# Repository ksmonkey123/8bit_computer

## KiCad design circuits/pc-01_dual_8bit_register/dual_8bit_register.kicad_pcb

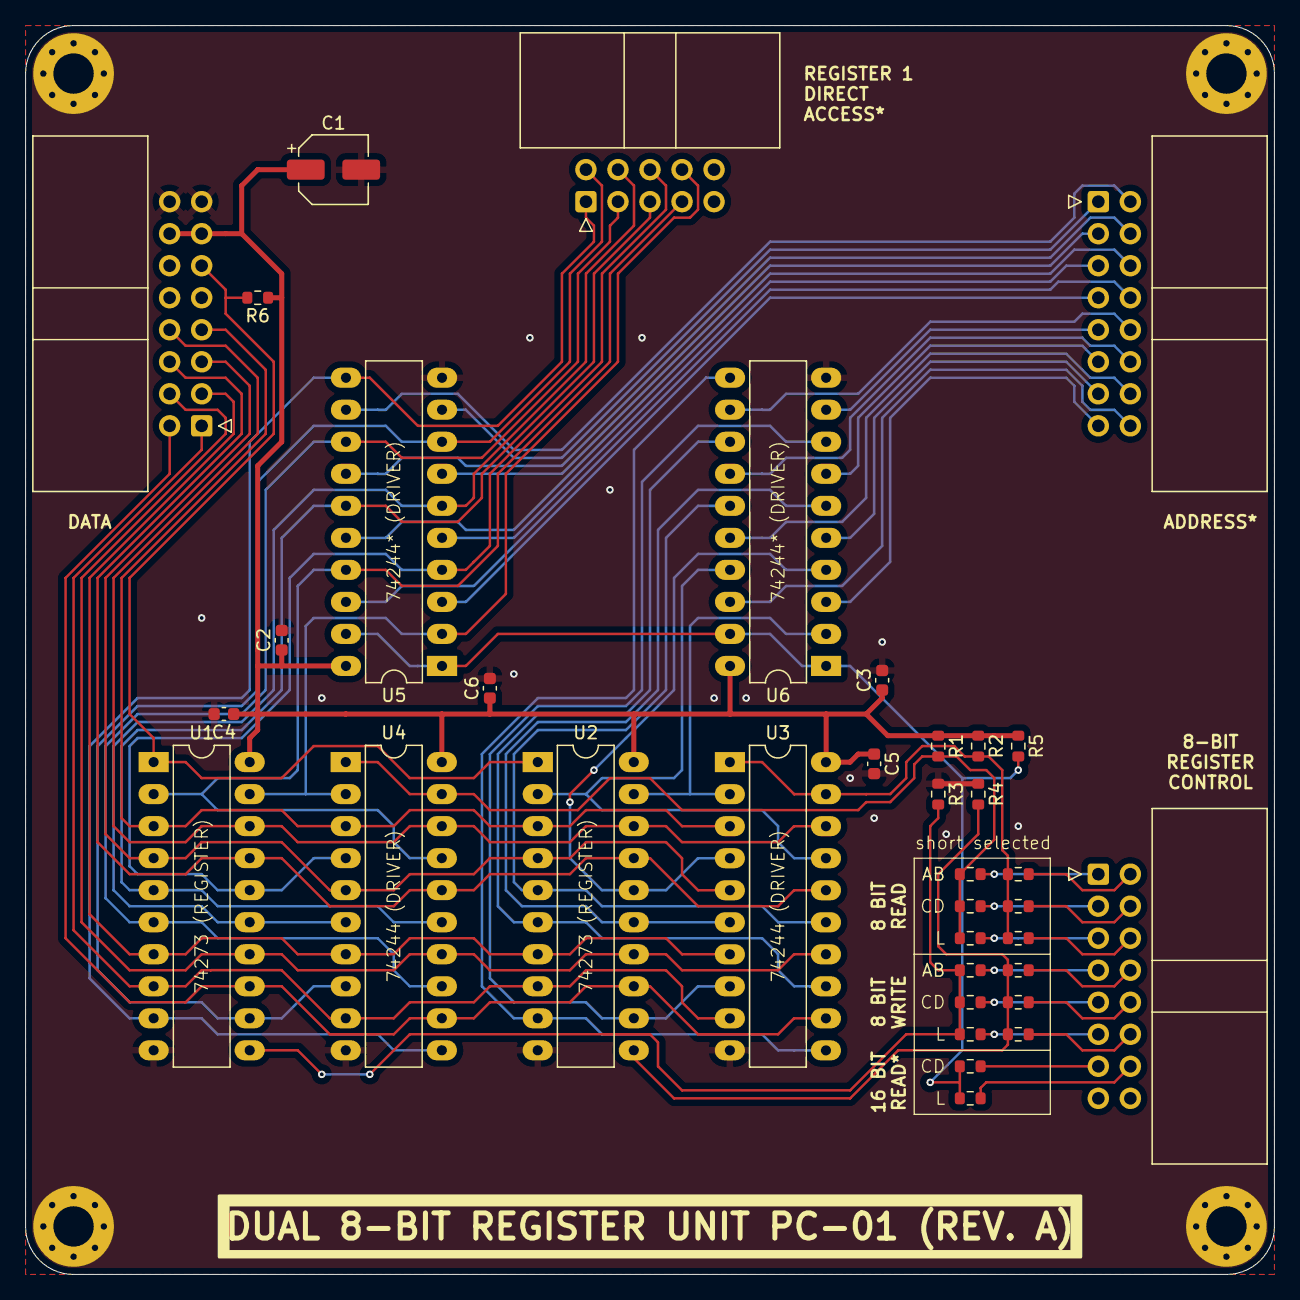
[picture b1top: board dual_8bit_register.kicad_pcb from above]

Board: 2 copper layers, 99.1 x 99.1 mm, 40 parts (0 on the bottom side), 62 nets.

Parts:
ADDRESS_BUS1: Conn_01x16; IDC-Header_2x08_P2.54mm_Horizontal
C1: C_Polarized; CP_Elec_5x5.3
C2, C3, C4, C5, C6: C; C_0603_1608Metric
CTRL_BUS1: Conn_01x16; IDC-Header_2x08_P2.54mm_Horizontal
DATA_BUS1: Conn_01x16; IDC-Header_2x08_P2.54mm_Horizontal
H1, H2, H3, H4: MountingHole_Pad; MountingHole_3.2mm_M3_Pad_Via
J1: Conn_01x10; IDC-Header_2x05_P2.54mm_Horizontal
R1, R2, R3, R4, R5, R6: R; R_0603_1608Metric
R_adrCD1: R; R_0603_1608Metric
R_adrL1: R; R_0603_1608Metric
R_readA1: R; R_0603_1608Metric
R_readB1: R; R_0603_1608Metric
R_readC1: R; R_0603_1608Metric
R_readD1: R; R_0603_1608Metric
R_readL1, R_readL2: R; R_0603_1608Metric
R_writeA1: R; R_0603_1608Metric
R_writeB1: R; R_0603_1608Metric
R_writeC1: R; R_0603_1608Metric
R_writeD1: R; R_0603_1608Metric
R_writeL1, R_writeL2: R; R_0603_1608Metric
U1, U2: 74HC273; DIP-20_W7.62mm_LongPads
U3, U4, U5, U6: 74HC244; DIP-20_W7.62mm_LongPads

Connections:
/adr0: ADDRESS_BUS1.1, U5.9 (2Y3)
/adr1: ADDRESS_BUS1.2, U5.12 (1Y3)
/adr2: ADDRESS_BUS1.3, U5.7 (2Y2)
/adr3: ADDRESS_BUS1.4, U5.14 (1Y2)
/adr4: ADDRESS_BUS1.5, U5.5 (2Y1)
/adr5: ADDRESS_BUS1.6, U5.16 (1Y1)
/adr6: ADDRESS_BUS1.7, U5.3 (2Y0)
/adr7: ADDRESS_BUS1.8, U5.18 (1Y0)
/adr8: ADDRESS_BUS1.9, U6.9 (2Y3)
/adr9: ADDRESS_BUS1.10, U6.12 (1Y3)
/adr10: ADDRESS_BUS1.11, U6.7 (2Y2)
/adr11: ADDRESS_BUS1.12, U6.14 (1Y2)
/adr12: ADDRESS_BUS1.13, U6.5 (2Y1)
/adr13: ADDRESS_BUS1.14, U6.16 (1Y1)
/adr14: ADDRESS_BUS1.15, U6.3 (2Y0)
/adr15: ADDRESS_BUS1.16, U6.18 (1Y0)
/d0: DATA_BUS1.1, U1.8 (D3), U2.8 (D3), U3.9 (2Y3), U4.9 (2Y3)
/d1: DATA_BUS1.2, U1.13 (D4), U2.13 (D4), U3.12 (1Y3), U4.12 (1Y3)
/d2: DATA_BUS1.3, U1.7 (D2), U2.7 (D2), U3.7 (2Y2), U4.7 (2Y2)
/d3: DATA_BUS1.4, U1.14 (D5), U2.14 (D5), U3.14 (1Y2), U4.14 (1Y2)
/d4: DATA_BUS1.5, U1.4 (D1), U2.4 (D1), U3.5 (2Y1), U4.5 (2Y1)
/d5: DATA_BUS1.6, U1.17 (D6), U2.17 (D6), U3.16 (1Y1), U4.16 (1Y1)
/d6: DATA_BUS1.7, U1.3 (D0), U2.3 (D0), U3.3 (2Y0), U4.3 (2Y0)
/d7: DATA_BUS1.8, U1.18 (D7), U2.18 (D7), U3.18 (1Y0), U4.18 (1Y0)
/writeA: CTRL_BUS1.7, R_writeA1.1
/writeB: CTRL_BUS1.8, R_writeB1.1
/writeC: CTRL_BUS1.9, R_writeC1.1
/writeD: CTRL_BUS1.10, R_writeD1.1
/writeL1: CTRL_BUS1.11, R_writeL1.1
/writeL2: CTRL_BUS1.12, R_writeL2.1
/~adrCD: CTRL_BUS1.13, R_adrCD1.2
/~adrL: CTRL_BUS1.14, R_adrL1.2
/~readA: CTRL_BUS1.1, R_readA1.2
/~readB: CTRL_BUS1.2, R_readB1.2
/~readC: CTRL_BUS1.3, R_readC1.2
/~readD: CTRL_BUS1.4, R_readD1.2
/~readL1: CTRL_BUS1.5, R_readL1.2
/~readL2: CTRL_BUS1.6, R_readL2.2
/~reset: DATA_BUS1.11, R6.2, U1.1 (~Mr), U2.1 (~Mr)
GND: C1.2, C2.2, C3.2, C4.2, C5.2, C6.2, DATA_BUS1.15, DATA_BUS1.16, H1.1, H2.1, H3.1, H4.1, R3.1, R4.1, U1.10 (GND), U2.10 (GND), U3.10 (GND), U4.10 (GND), U5.10 (GND), U6.10 (GND)
unnamed: J1.1, U1.9 (Q3), U4.11 (2A3), U5.11 (2A3)
unnamed: J1.2, U1.12 (Q4), U4.8 (1A3), U5.8 (1A3)
unnamed: J1.3, U1.6 (Q2), U4.13 (2A2), U5.13 (2A2)
unnamed: J1.4, U1.15 (Q5), U4.6 (1A2), U5.6 (1A2)
unnamed: J1.5, U1.5 (Q1), U4.15 (2A1), U5.15 (2A1)
unnamed: J1.6, U1.16 (Q6), U4.4 (1A1), U5.4 (1A1)
unnamed: J1.7, U1.2 (Q0), U4.17 (2A0), U5.17 (2A0)
unnamed: J1.8, U1.19 (Q7), U4.2 (1A0), U5.2 (1A0)
unnamed: R3.2, R_writeA1.2, R_writeC1.2, R_writeL1.2, U1.11 (Cp)
unnamed: R4.2, R_writeB1.2, R_writeD1.2, R_writeL2.2, U2.11 (Cp)
unnamed: U2.2 (Q0), U3.17 (2A0), U6.17 (2A0)
unnamed: U2.5 (Q1), U3.15 (2A1), U6.15 (2A1)
unnamed: U2.6 (Q2), U3.13 (2A2), U6.13 (2A2)
unnamed: U2.9 (Q3), U3.11 (2A3), U6.11 (2A3)
unnamed: U2.12 (Q4), U3.8 (1A3), U6.8 (1A3)
unnamed: U2.15 (Q5), U3.6 (1A2), U6.6 (1A2)
unnamed: U2.16 (Q6), U3.4 (1A1), U6.4 (1A1)
unnamed: U2.19 (Q7), U3.2 (1A0), U6.2 (1A0)
unnamed: R2.2, R_readB1.1, R_readD1.1, R_readL2.1, U3.1 (1OE), U3.19 (2OE)
unnamed: R1.2, R_readA1.1, R_readC1.1, R_readL1.1, U4.1 (1OE), U4.19 (2OE)
unnamed: R5.2, R_adrCD1.1, R_adrL1.1, U5.1 (1OE), U5.19 (2OE), U6.1 (1OE), U6.19 (2OE)
VCC: C1.1, C2.1, C3.1, C4.1, C5.1, C6.1, DATA_BUS1.13, DATA_BUS1.14, R1.1, R2.1, R5.1, R6.1, U1.20 (VCC), U2.20 (VCC), U3.20 (VCC), U4.20 (VCC), U5.20 (VCC), U6.20 (VCC)

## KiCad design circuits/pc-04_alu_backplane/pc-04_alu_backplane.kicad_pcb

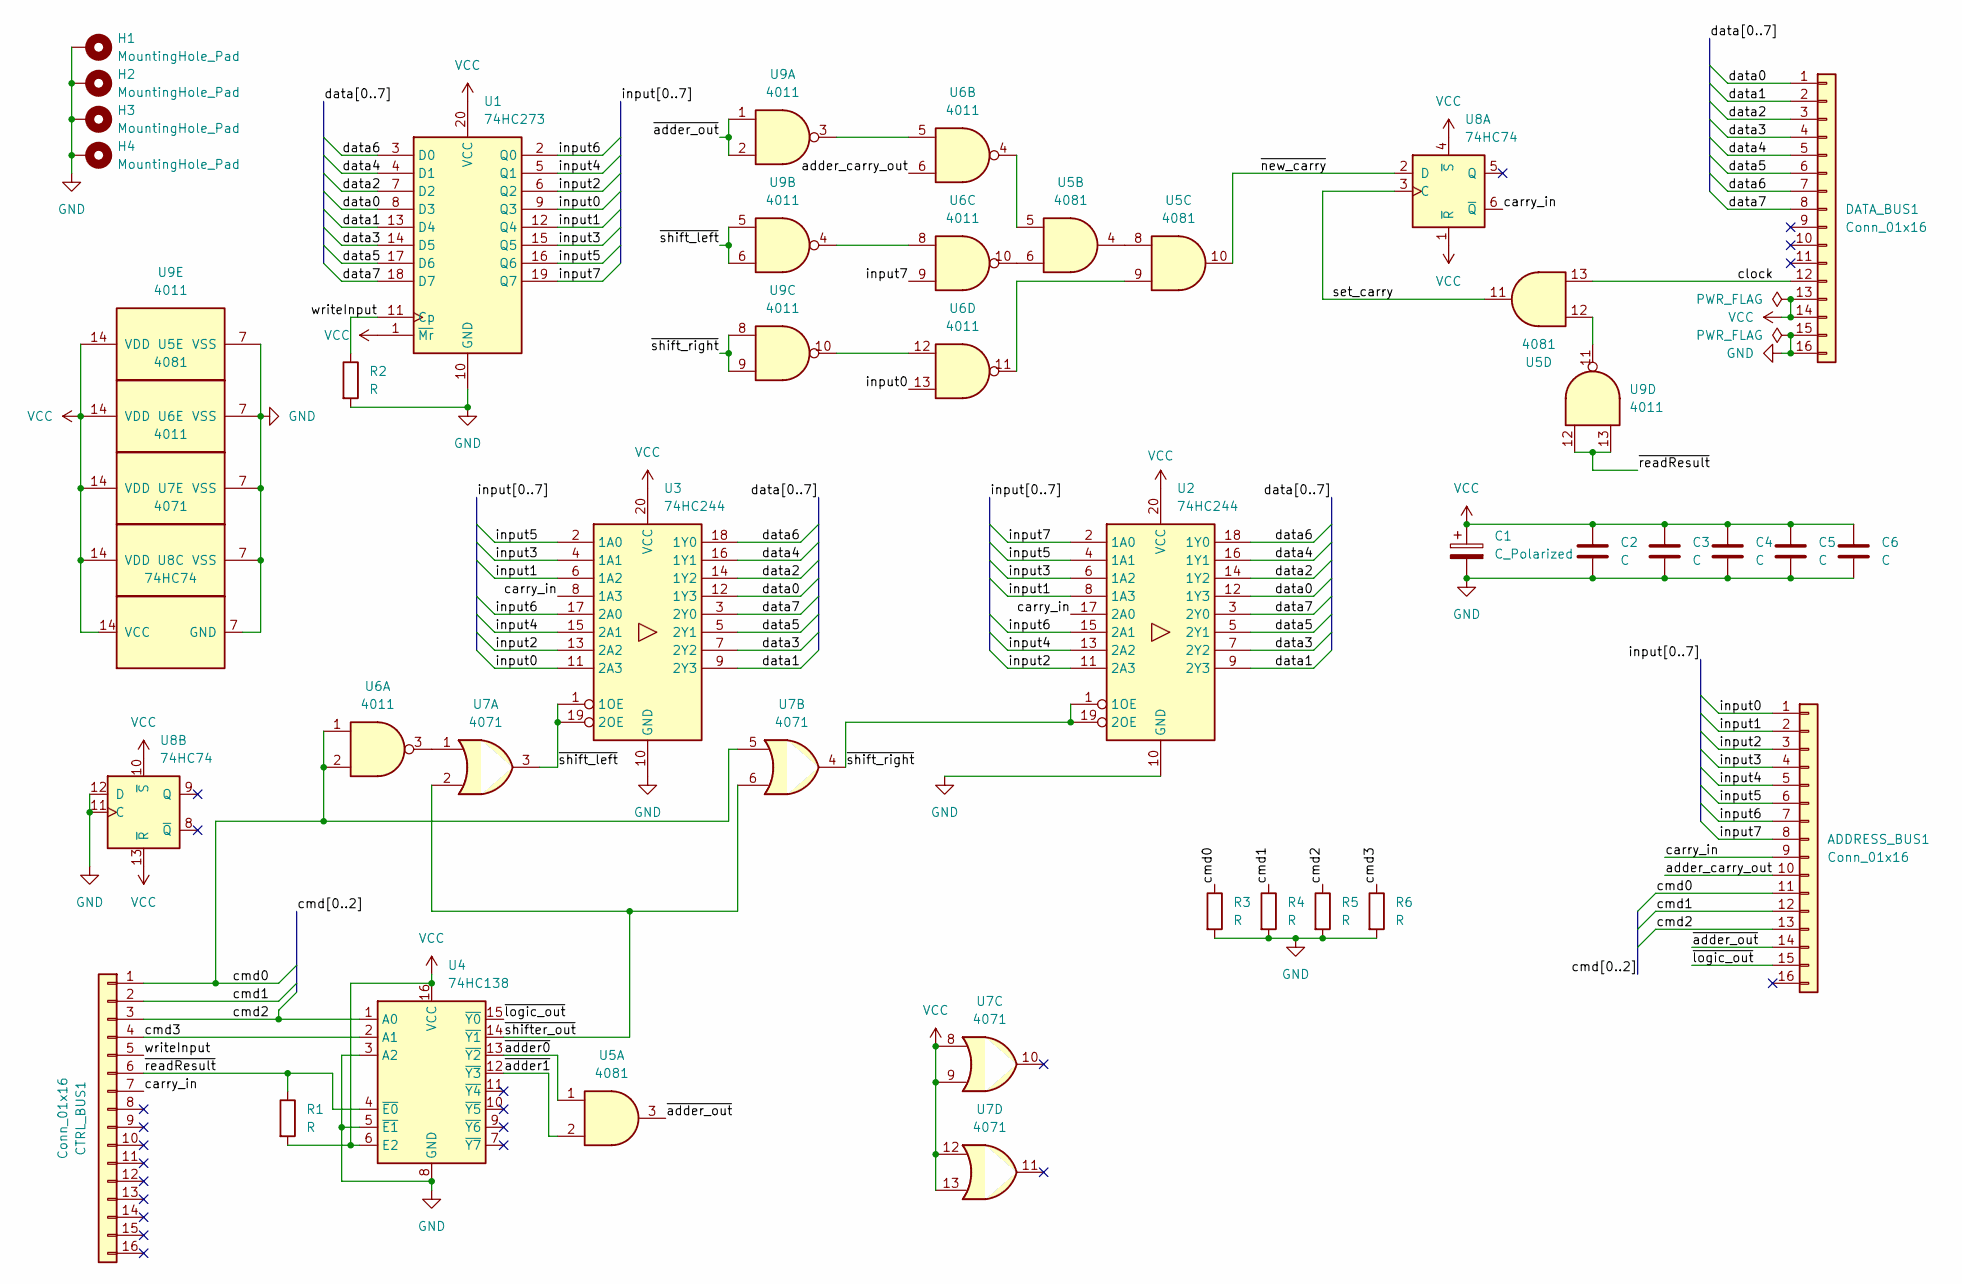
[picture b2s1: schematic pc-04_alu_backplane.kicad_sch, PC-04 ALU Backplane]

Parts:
ADDRESS_BUS1: Conn_01x16; IDC-Header_2x08_P2.54mm_Horizontal
C1: C_Polarized; CP_Elec_5x5.3
C2, C3, C4, C5, C6: C; C_0603_1608Metric
CTRL_BUS1: Conn_01x16; IDC-Header_2x08_P2.54mm_Horizontal
DATA_BUS1: Conn_01x16; IDC-Header_2x08_P2.54mm_Horizontal
H1, H2, H3, H4: MountingHole_Pad; MountingHole_3.2mm_M3_Pad_Via
R1, R2, R3, R4, R5, R6: R; R_0603_1608Metric
U1: 74HC273; DIP-20_W7.62mm_LongPads
U2, U3: 74HC244; DIP-20_W7.62mm_LongPads
U4: 74HC138; DIP-16_W7.62mm_LongPads
U5: 4081; DIP-14_W7.62mm_LongPads
U6, U9: 4011; DIP-14_W7.62mm_LongPads
U7: 4071; DIP-14_W7.62mm_LongPads
U8: 74HC74; DIP-14_W7.62mm_LongPads

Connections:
/adder_carry_out: ADDRESS_BUS1.10, U6.6
/carry_in: ADDRESS_BUS1.9, CTRL_BUS1.7, U2.17 (2A0), U3.8 (1A3), U8.6 (~Q)
/clock: DATA_BUS1.12, U5.13
/cmd0: ADDRESS_BUS1.11, CTRL_BUS1.1, R3.1, U6.1, U6.2, U7.5
/cmd1: ADDRESS_BUS1.12, CTRL_BUS1.2, R4.1
/cmd2: ADDRESS_BUS1.13, CTRL_BUS1.3, R5.1, U4.1 (A0)
/cmd3: CTRL_BUS1.4, R6.1, U4.2 (A1)
/data0: DATA_BUS1.1, U1.8 (D3), U2.12 (1Y3), U3.12 (1Y3)
/data1: DATA_BUS1.2, U1.13 (D4), U2.9 (2Y3), U3.9 (2Y3)
/data2: DATA_BUS1.3, U1.7 (D2), U2.14 (1Y2), U3.14 (1Y2)
/data3: DATA_BUS1.4, U1.14 (D5), U2.7 (2Y2), U3.7 (2Y2)
/data4: DATA_BUS1.5, U1.4 (D1), U2.16 (1Y1), U3.16 (1Y1)
/data5: DATA_BUS1.6, U1.17 (D6), U2.5 (2Y1), U3.5 (2Y1)
/data6: DATA_BUS1.7, U1.3 (D0), U2.18 (1Y0), U3.18 (1Y0)
/data7: DATA_BUS1.8, U1.18 (D7), U2.3 (2Y0), U3.3 (2Y0)
/input0: ADDRESS_BUS1.1, U1.9 (Q3), U3.11 (2A3), U6.13
/input1: ADDRESS_BUS1.2, U1.12 (Q4), U2.8 (1A3), U3.6 (1A2)
/input2: ADDRESS_BUS1.3, U1.6 (Q2), U2.11 (2A3), U3.13 (2A2)
/input3: ADDRESS_BUS1.4, U1.15 (Q5), U2.6 (1A2), U3.4 (1A1)
/input4: ADDRESS_BUS1.5, U1.5 (Q1), U2.13 (2A2), U3.15 (2A1)
/input5: ADDRESS_BUS1.6, U1.16 (Q6), U2.4 (1A1), U3.2 (1A0)
/input6: ADDRESS_BUS1.7, U1.2 (Q0), U2.15 (2A1), U3.17 (2A0)
/input7: ADDRESS_BUS1.8, U1.19 (Q7), U2.2 (1A0), U6.9
/set_carry: U5.11, U8.3 (C)
/writeInput: CTRL_BUS1.5, R2.1, U1.11 (Cp)
/~adder0: U4.13 (~Y2), U5.1
/~adder1: U4.12 (~Y3), U5.2
/~adder_out: ADDRESS_BUS1.14, U5.3, U9.1, U9.2
/~logic_out: ADDRESS_BUS1.15, U4.15 (~Y0)
/~new_carry: U5.10, U8.2 (D)
/~readResult: CTRL_BUS1.6, R1.1, U4.4 (~E0), U9.12, U9.13
/~shift_left: U3.1 (1OE), U3.19 (2OE), U7.3, U9.5, U9.6
/~shift_right: U2.1 (1OE), U2.19 (2OE), U7.4, U9.8, U9.9
/~shifter_out: U4.14 (~Y1), U7.2, U7.6
GND: C1.2, C2.2, C3.2, C4.2, C5.2, C6.2, DATA_BUS1.15, DATA_BUS1.16, H1.1, H2.1, H3.1, H4.1, R2.2, R3.2, R4.2, R5.2, R6.2, U1.10 (GND), U2.10 (GND), U3.10 (GND), U4.3 (A2), U4.5 (~E1), U4.8 (GND), U5.7 (VSS), U6.7 (VSS), U7.7 (VSS), U8.7 (GND), U8.11 (C), U8.12 (D), U9.7 (VSS)
unnamed: U5.4, U5.8
unnamed: U5.5, U6.4
unnamed: U5.6, U6.10
unnamed: U5.9, U6.11
unnamed: U5.12, U9.11
unnamed: U6.3, U7.1
unnamed: U6.5, U9.3
unnamed: U6.8, U9.4
unnamed: U6.12, U9.10
VCC: C1.1, C2.1, C3.1, C4.1, C5.1, C6.1, DATA_BUS1.13, DATA_BUS1.14, R1.2, U1.1 (~Mr), U1.20 (VCC), U2.20 (VCC), U3.20 (VCC), U4.6 (E2), U4.16 (VCC), U5.14 (VDD), U6.14 (VDD), U7.8, U7.9, U7.12, U7.13, U7.14 (VDD), U8.1 (~R), U8.4 (~S), U8.10 (~S), U8.13 (~R), U8.14 (VCC), U9.14 (VDD)

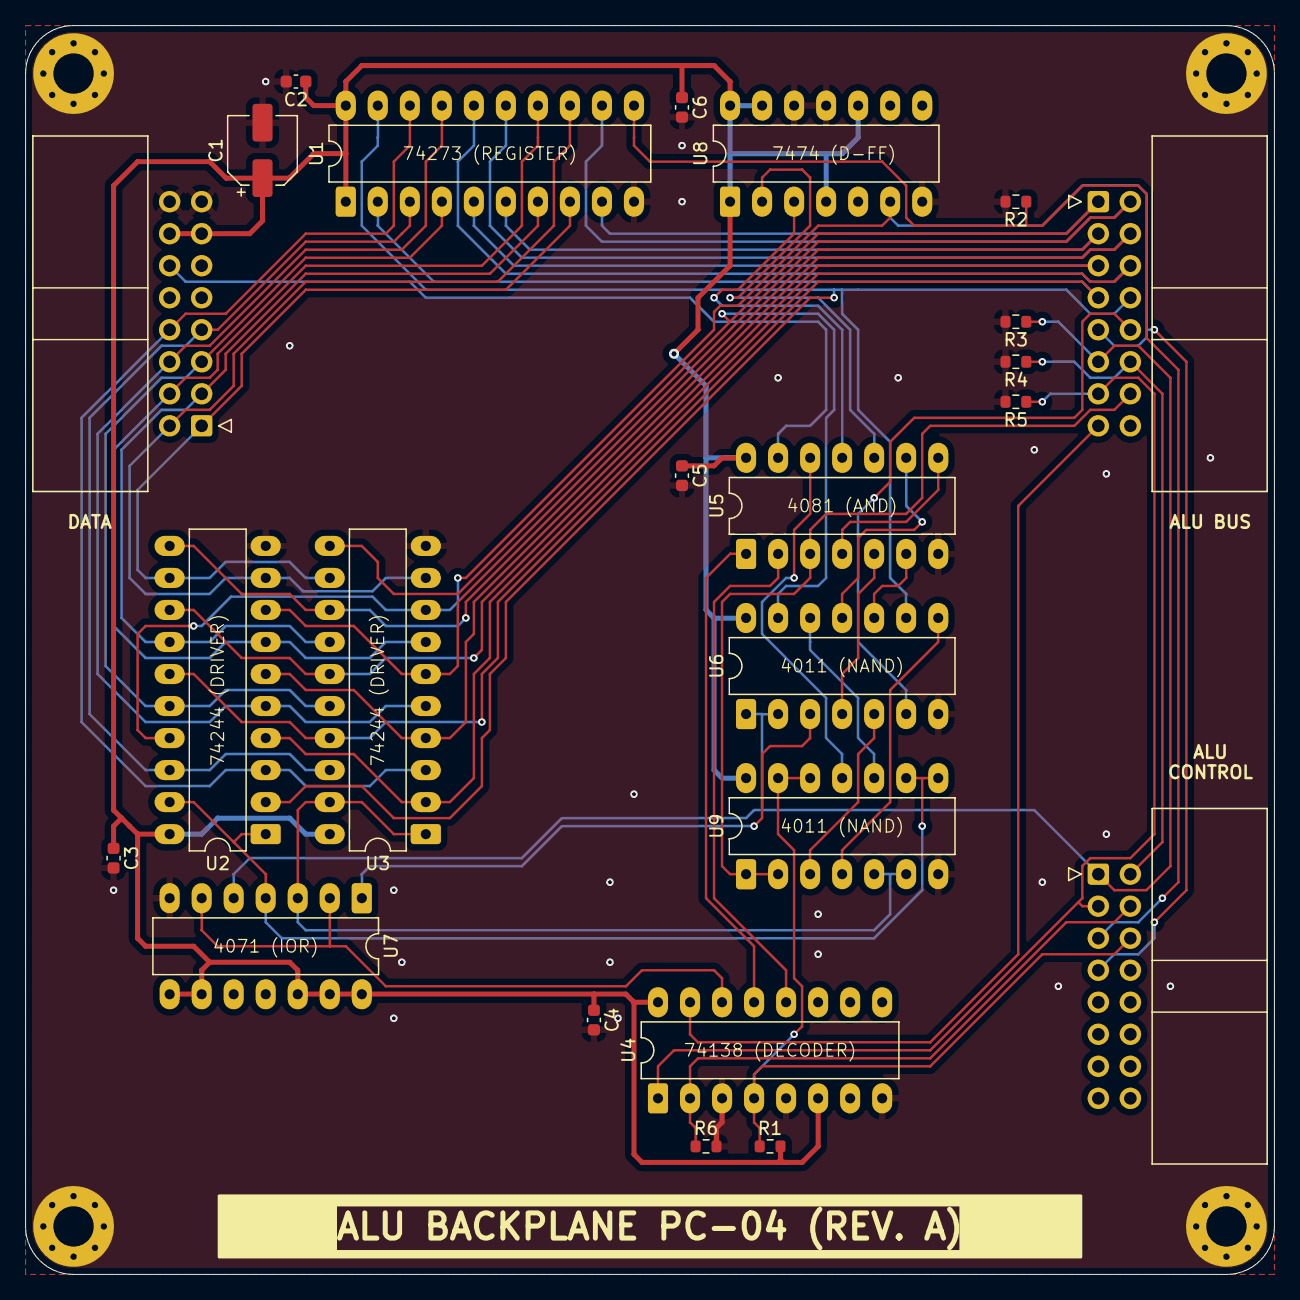
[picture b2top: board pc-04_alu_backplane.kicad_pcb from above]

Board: 2 copper layers, 99.1 x 99.1 mm, 28 parts (0 on the bottom side), 45 nets.

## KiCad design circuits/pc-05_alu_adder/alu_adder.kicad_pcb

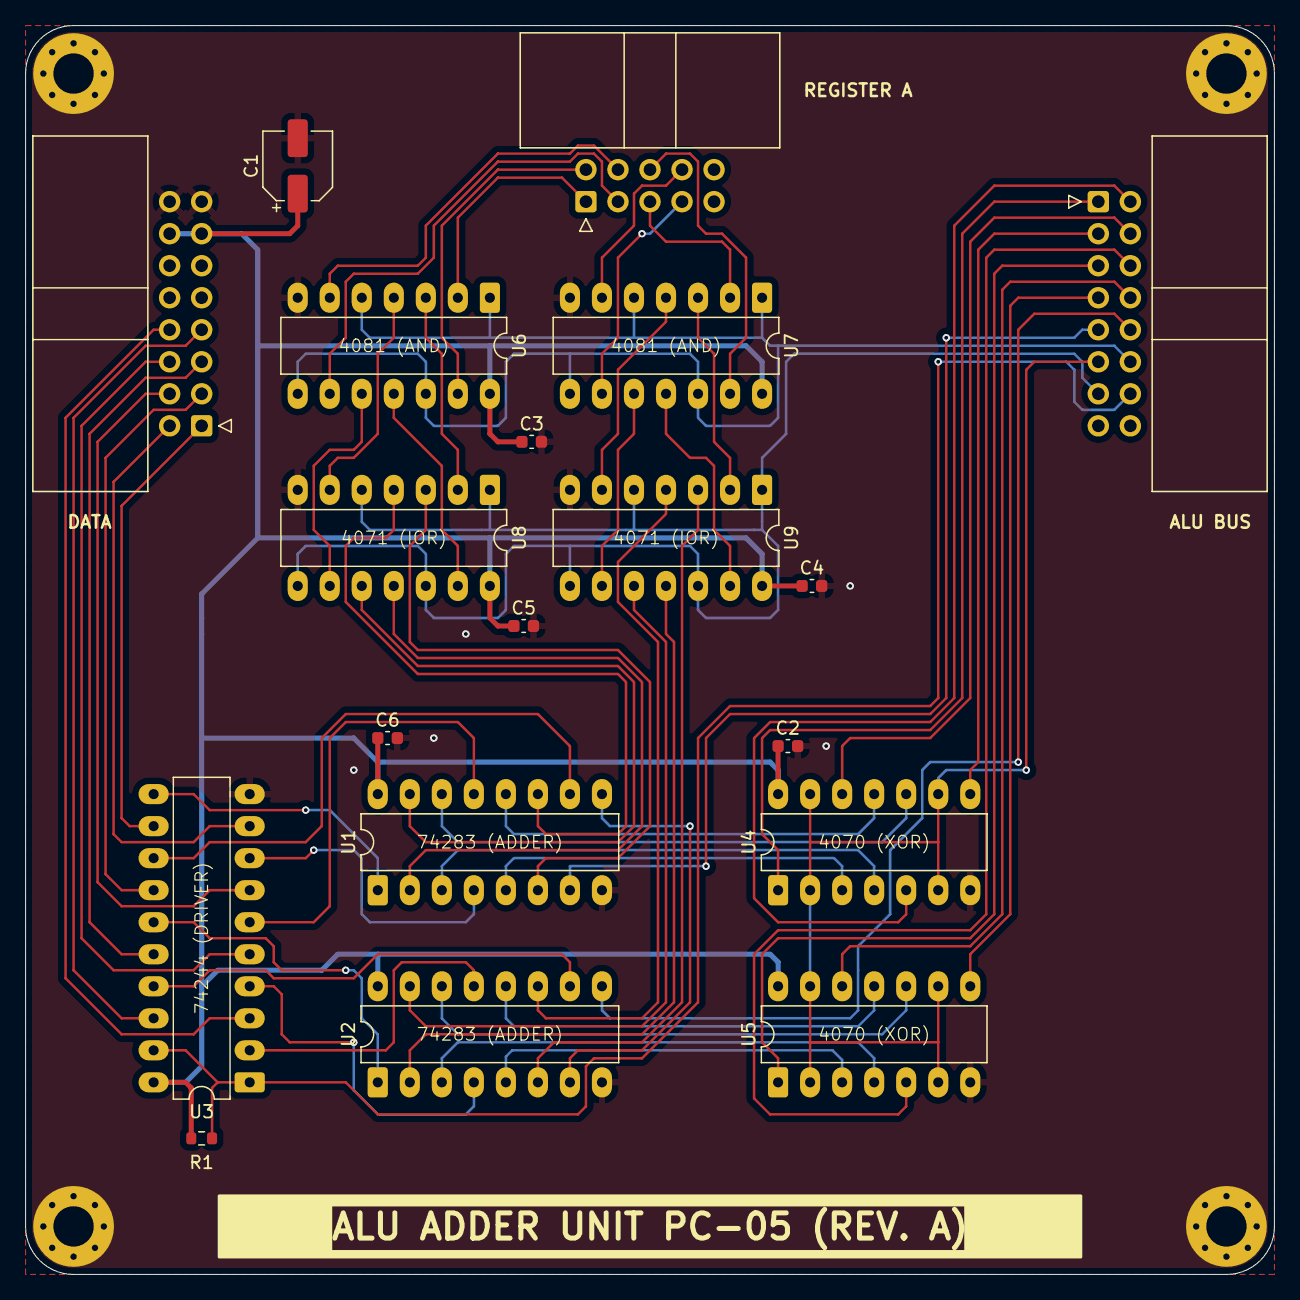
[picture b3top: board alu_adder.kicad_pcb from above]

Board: 2 copper layers, 99.1 x 99.1 mm, 23 parts (0 on the bottom side), 65 nets.

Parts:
ADDRESS_BUS1: Conn_01x16; IDC-Header_2x08_P2.54mm_Horizontal
C1: C_Polarized; CP_Elec_5x5.3
C2, C3, C4, C5, C6: C; C_0603_1608Metric
DATA_BUS1: Conn_01x16; IDC-Header_2x08_P2.54mm_Horizontal
H1, H2, H3, H4: MountingHole_Pad; MountingHole_3.2mm_M3_Pad_Via
J1: Conn_01x10; IDC-Header_2x05_P2.54mm_Horizontal
R1: 100k; R_0603_1608Metric
U1, U2: 74LS283; DIP-16_W7.62mm_LongPads
U3: 74AHC244; DIP-20_W7.62mm_LongPads
U4, U5: 4070; DIP-14_W7.62mm_LongPads
U6, U7: 4081; DIP-14_W7.62mm_LongPads
U8, U9: 4071; DIP-14_W7.62mm_LongPads

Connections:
/adder_a0: U1.5 (A1), U4.3
/adder_a1: U1.3 (A2), U4.4
/adder_a2: U1.14 (A3), U4.10
/adder_a3: U1.12 (A4), U4.11
/adder_a4: U2.5 (A1), U5.3
/adder_a5: U2.3 (A2), U5.4
/adder_a6: U2.14 (A3), U5.10
/adder_a7: U2.12 (A4), U5.11
/adder_b0: U1.6 (B1), U8.3
/adder_b1: U1.2 (B2), U8.11
/adder_b2: U1.15 (B3), U8.10
/adder_b3: U1.11 (B4), U8.4
/adder_b4: U2.6 (B1), U9.3
/adder_b5: U2.2 (B2), U9.11
/adder_b6: U2.15 (B3), U9.10
/adder_b7: U2.11 (B4), U9.4
/adder_carry_out: ADDRESS_BUS1.10, U2.9 (C4)
/carry_in: ADDRESS_BUS1.9, U1.7 (C0)
/cmd0: ADDRESS_BUS1.11, U4.2, U4.6, U4.9, U4.13, U5.2, U5.6, U5.9, U5.13
/cmd1: ADDRESS_BUS1.12, U6.1, U6.5, U6.8, U6.12, U7.1, U7.5, U7.8, U7.12
/cmd2: ADDRESS_BUS1.13, U8.1, U8.5, U8.8, U8.12, U9.1, U9.5, U9.8, U9.12
/data0: DATA_BUS1.1, U3.12 (1Y3)
/data1: DATA_BUS1.2, U3.9 (2Y3)
/data2: DATA_BUS1.3, U3.14 (1Y2)
/data3: DATA_BUS1.4, U3.7 (2Y2)
/data4: DATA_BUS1.5, U3.16 (1Y1)
/data5: DATA_BUS1.6, U3.5 (2Y1)
/data6: DATA_BUS1.7, U3.18 (1Y0)
/data7: DATA_BUS1.8, U3.3 (2Y0)
/input0: ADDRESS_BUS1.1, U4.1
/input1: ADDRESS_BUS1.2, U4.5
/input2: ADDRESS_BUS1.3, U4.8
/input3: ADDRESS_BUS1.4, U4.12
/input4: ADDRESS_BUS1.5, U5.1
/input5: ADDRESS_BUS1.6, U5.5
/input6: ADDRESS_BUS1.7, U5.8
/input7: ADDRESS_BUS1.8, U5.12
/rega0: J1.1, U6.2
/rega1: J1.2, U6.13
/rega2: J1.3, U6.9
/rega3: J1.4, U6.6
/rega4: J1.5, U7.2
/rega5: J1.6, U7.13
/rega6: J1.7, U7.9
/rega7: J1.8, U7.6
/sum0: U1.4 (S1), U3.8 (1A3)
/sum1: U1.1 (S2), U3.11 (2A3)
/sum2: U1.13 (S3), U3.6 (1A2)
/sum3: U1.10 (S4), U3.13 (2A2)
/sum4: U2.4 (S1), U3.4 (1A1)
/sum5: U2.1 (S2), U3.15 (2A1)
/sum6: U2.13 (S3), U3.2 (1A0)
/sum7: U2.10 (S4), U3.17 (2A0)
/~adder_out: ADDRESS_BUS1.14, R1.2, U3.1 (1OE), U3.19 (2OE)
GND: C1.2, C2.2, C3.2, C4.2, C5.2, C6.2, DATA_BUS1.15, DATA_BUS1.16, H1.1, H2.1, H3.1, H4.1, U1.8 (GND), U2.8 (GND), U3.10 (GND), U4.7 (VSS), U5.7 (VSS), U6.7 (VSS), U7.7 (VSS), U8.7 (VSS), U9.7 (VSS)
unnamed: U1.9 (C4), U2.7 (C0)
unnamed: U6.3, U8.2
unnamed: U6.4, U8.6
unnamed: U6.10, U8.9
unnamed: U6.11, U8.13
unnamed: U7.3, U9.2
unnamed: U7.4, U9.6
unnamed: U7.10, U9.9
unnamed: U7.11, U9.13
VCC: C1.1, C2.1, C3.1, C4.1, C5.1, C6.1, DATA_BUS1.13, DATA_BUS1.14, R1.1, U1.16 (VCC), U2.16 (VCC), U3.20 (VCC), U4.14 (VDD), U5.14 (VDD), U6.14 (VDD), U7.14 (VDD), U8.14 (VDD), U9.14 (VDD)

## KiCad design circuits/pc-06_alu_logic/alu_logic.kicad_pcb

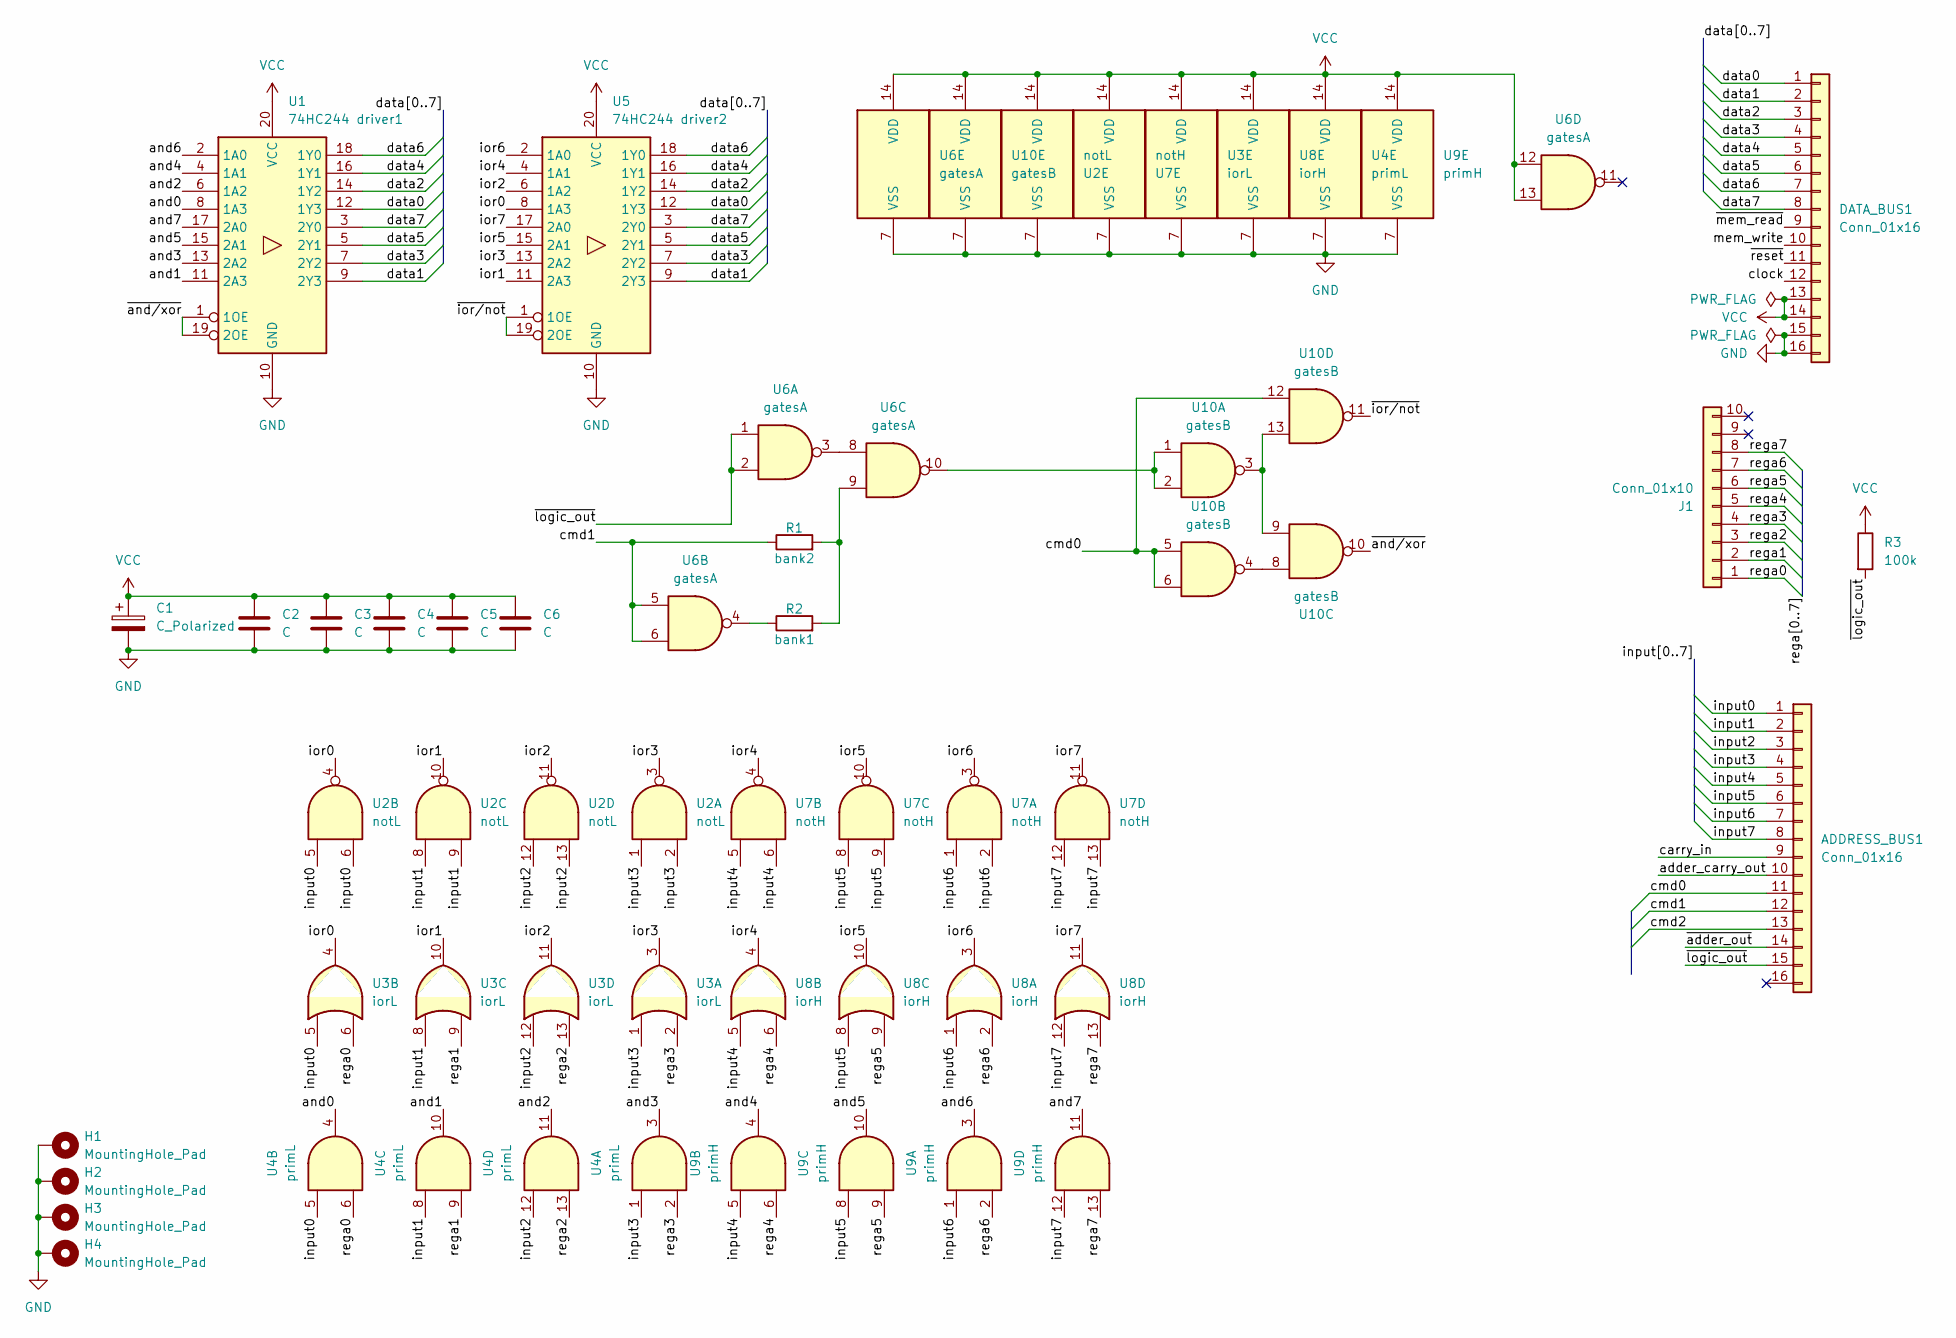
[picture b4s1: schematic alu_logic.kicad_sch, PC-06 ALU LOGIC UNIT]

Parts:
ADDRESS_BUS1: Conn_01x16; IDC-Header_2x08_P2.54mm_Horizontal
C1: C_Polarized; CP_Elec_5x5.3
C2, C3, C4, C5, C6: C; C_0603_1608Metric
DATA_BUS1: Conn_01x16; IDC-Header_2x08_P2.54mm_Horizontal
H1, H2, H3, H4: MountingHole_Pad; MountingHole_3.2mm_M3_Pad_Via
J1: Conn_01x10; IDC-Header_2x05_P2.54mm_Horizontal
R1: bank2; R_0603_1608Metric
R2: bank1; R_0603_1608Metric
R3: 100k; R_0603_1608Metric
U1: 74HC244 driver1; DIP-20_W7.62mm_LongPads
U2: notL; DIP-14_W7.62mm_LongPads
U3: iorL; DIP-14_W7.62mm_LongPads
U4: primL; DIP-14_W7.62mm_LongPads
U5: 74HC244 driver2; DIP-20_W7.62mm_LongPads
U6: gatesA; DIP-14_W7.62mm_LongPads
U7: notH; DIP-14_W7.62mm_LongPads
U8: iorH; DIP-14_W7.62mm_LongPads
U9: primH; DIP-14_W7.62mm_LongPads
U10: gatesB; DIP-14_W7.62mm_LongPads

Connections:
/adder_carry_out: ADDRESS_BUS1.10
/and0: U1.8 (1A3), U4.4
/and1: U1.11 (2A3), U4.10
/and2: U1.6 (1A2), U4.11
/and3: U1.13 (2A2), U4.3
/and4: U1.4 (1A1), U9.4
/and5: U1.15 (2A1), U9.10
/and6: U1.2 (1A0), U9.3
/and7: U1.17 (2A0), U9.11
/carry_in: ADDRESS_BUS1.9
/clock: DATA_BUS1.12
/cmd0: ADDRESS_BUS1.11, U10.5, U10.6, U10.12
/cmd1: ADDRESS_BUS1.12, R1.1, U6.5, U6.6
/cmd2: ADDRESS_BUS1.13
/data0: DATA_BUS1.1, U1.12 (1Y3), U5.12 (1Y3)
/data1: DATA_BUS1.2, U1.9 (2Y3), U5.9 (2Y3)
/data2: DATA_BUS1.3, U1.14 (1Y2), U5.14 (1Y2)
/data3: DATA_BUS1.4, U1.7 (2Y2), U5.7 (2Y2)
/data4: DATA_BUS1.5, U1.16 (1Y1), U5.16 (1Y1)
/data5: DATA_BUS1.6, U1.5 (2Y1), U5.5 (2Y1)
/data6: DATA_BUS1.7, U1.18 (1Y0), U5.18 (1Y0)
/data7: DATA_BUS1.8, U1.3 (2Y0), U5.3 (2Y0)
/input0: ADDRESS_BUS1.1, U2.5, U2.6, U3.5, U4.5
/input1: ADDRESS_BUS1.2, U2.8, U2.9, U3.8, U4.8
/input2: ADDRESS_BUS1.3, U2.12, U2.13, U3.12, U4.12
/input3: ADDRESS_BUS1.4, U2.1, U2.2, U3.1, U4.1
/input4: ADDRESS_BUS1.5, U7.5, U7.6, U8.5, U9.5
/input5: ADDRESS_BUS1.6, U7.8, U7.9, U8.8, U9.8
/input6: ADDRESS_BUS1.7, U7.1, U7.2, U8.1, U9.1
/input7: ADDRESS_BUS1.8, U7.12, U7.13, U8.12, U9.12
/ior0: U2.4, U3.4, U5.8 (1A3)
/ior1: U2.10, U3.10, U5.11 (2A3)
/ior2: U2.11, U3.11, U5.6 (1A2)
/ior3: U2.3, U3.3, U5.13 (2A2)
/ior4: U5.4 (1A1), U7.4, U8.4
/ior5: U5.15 (2A1), U7.10, U8.10
/ior6: U5.2 (1A0), U7.3, U8.3
/ior7: U5.17 (2A0), U7.11, U8.11
/mem_write: DATA_BUS1.10
/rega0: J1.1, U3.6, U4.6
/rega1: J1.2, U3.9, U4.9
/rega2: J1.3, U3.13, U4.13
/rega3: J1.4, U3.2, U4.2
/rega4: J1.5, U8.6, U9.6
/rega5: J1.6, U8.9, U9.9
/rega6: J1.7, U8.2, U9.2
/rega7: J1.8, U8.13, U9.13
/~adder_out: ADDRESS_BUS1.14
/~and/xor: U1.1 (1OE), U1.19 (2OE), U10.10
/~ior/not: U5.1 (1OE), U5.19 (2OE), U10.11
/~logic_out: ADDRESS_BUS1.15, R3.2, U6.1, U6.2
/~mem_read: DATA_BUS1.9
/~reset: DATA_BUS1.11
GND: C1.2, C2.2, C3.2, C4.2, C5.2, C6.2, DATA_BUS1.15, DATA_BUS1.16, H1.1, H2.1, H3.1, H4.1, U1.10 (GND), U2.7 (VSS), U3.7 (VSS), U4.7 (VSS), U5.10 (GND), U6.7 (VSS), U7.7 (VSS), U8.7 (VSS), U9.7 (VSS), U10.7 (VSS)
unnamed: R1.2, R2.2, U6.9
unnamed: R2.1, U6.4
unnamed: U6.3, U6.8
unnamed: U6.10, U10.1, U10.2
unnamed: U10.4, U10.8
unnamed: U10.3, U10.9, U10.13
VCC: C1.1, C2.1, C3.1, C4.1, C5.1, C6.1, DATA_BUS1.13, DATA_BUS1.14, R3.1, U1.20 (VCC), U2.14 (VDD), U3.14 (VDD), U4.14 (VDD), U5.20 (VCC), U6.12, U6.13, U6.14 (VDD), U7.14 (VDD), U8.14 (VDD), U9.14 (VDD), U10.14 (VDD)

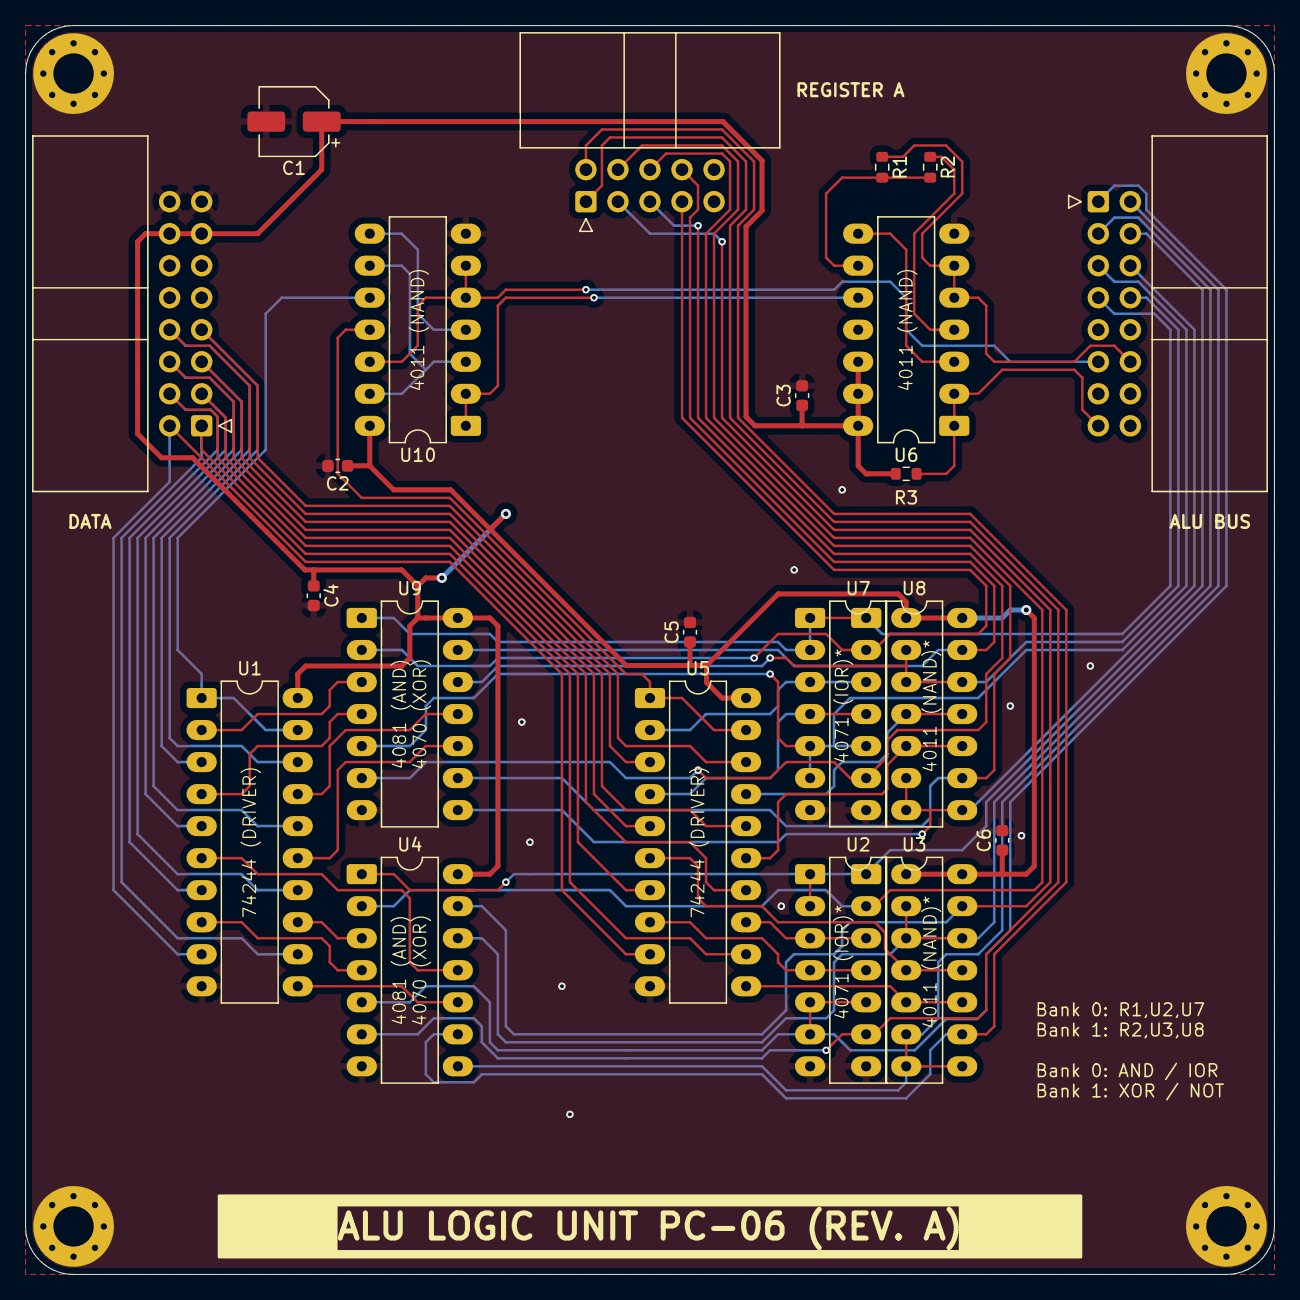
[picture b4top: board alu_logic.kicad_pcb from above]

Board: 2 copper layers, 99.1 x 99.1 mm, 26 parts (0 on the bottom side), 53 nets.
